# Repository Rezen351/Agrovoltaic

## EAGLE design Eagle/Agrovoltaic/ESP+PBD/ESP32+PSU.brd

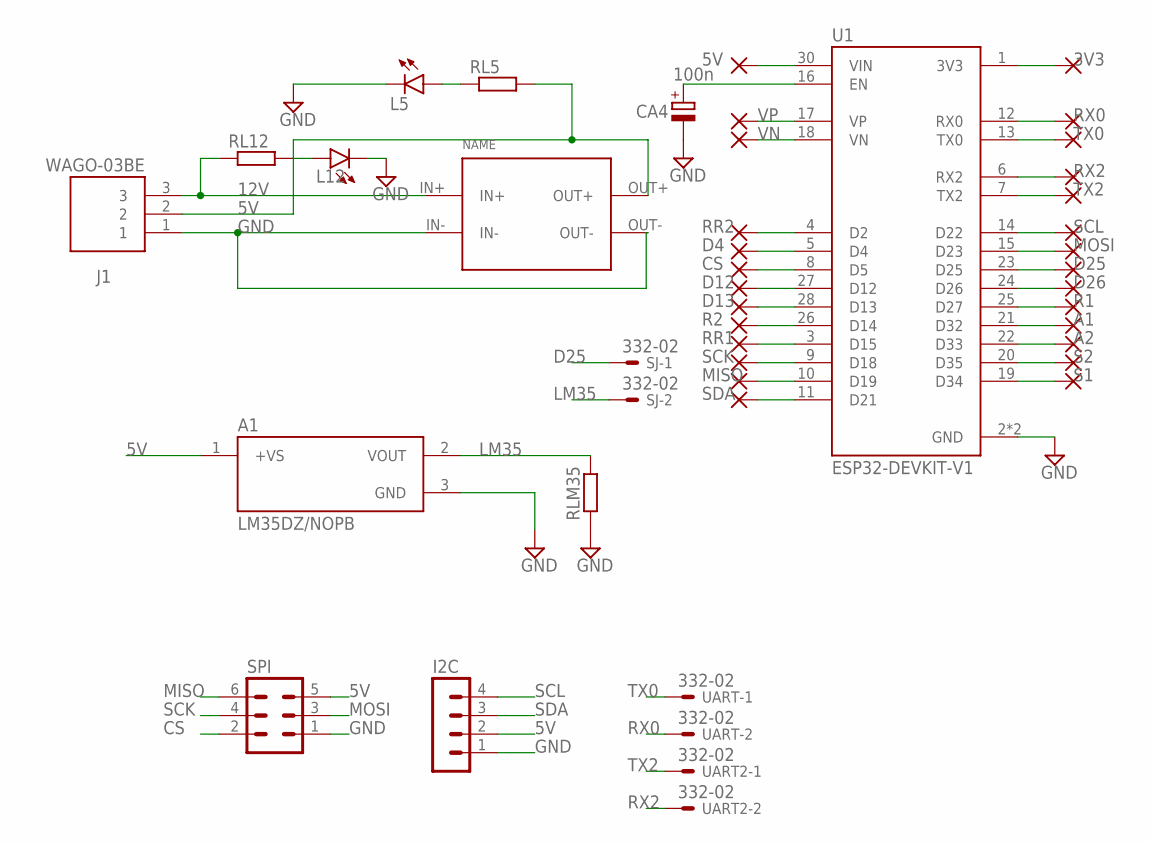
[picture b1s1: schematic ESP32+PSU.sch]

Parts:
A1: LM35DZ/NOPB; TO92127P521H735-3
CA4: 100n; E5-6
I2C: MA04-1
J1: WAGO-03BE; CUI_TB006-508-03BE
L5, L12: LED3MM
PAD1, PAD2, PAD3, PAD4, PAD5, PAD6, PAD7, PAD8, PAD9, PAD10, PAD11, PAD12, PAD13, PAD14, PAD15, PAD16, PAD17, PAD18, PAD19, PAD20, PAD21, PAD22, PAD23, PAD24, PAD25, PAD26, PAD52: WIREPAD1,6/0,9; 1,6/0,9
RL5, RL12: R-EU_0309/12; 0309/12
RLM35: R-EU_0309/12; 0309/12
SJ: 332-02
SPI: MA03-2
U1: ESP32-DEVKIT-V1; MODULE_ESP32_DEVKIT_V1
U$1: CP8-ADJ
UART, UART2: 332-02

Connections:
3V3: PAD11.1, U1.1 (3V3)
5V: A1.1 (+VS), I2C.2, J1.2, PAD25.1, RL5.2, SPI.5, U1.30 (VIN), U$1.OUT+
12V: J1.3, RL12.1, U$1.IN+
A1: PAD21.1, U1.21 (D32)
A2: PAD22.1, U1.22 (D33)
CS: PAD3.1, SPI.2, U1.8 (D5)
D4: PAD2.1, U1.5 (D4)
D12: PAD4.1, U1.27 (D12)
D13: PAD5.1, U1.28 (D13)
D25: PAD18.1, SJ.1, U1.23 (D25)
D26: PAD19.1, U1.24 (D26)
GND: A1.3 (GND), CA4.-, I2C.1, J1.1, L5.K (C), L12.K (C), RLM35.1, SPI.1, U1.2 (GND), U1.29 (GND), U$1.IN-, U$1.OUT-
LM35: A1.2 (VOUT), RLM35.2, SJ.2
MISO: PAD9.1, SPI.6, U1.10 (D19)
MOSI: PAD17.1, SPI.3, U1.15 (D23)
unnamed: L12.A, RL12.2
unnamed: L5.A, RL5.1
unnamed: CA4.+, U1.16 (EN)
R1: PAD20.1, U1.25 (D27)
R2: PAD6.1, U1.26 (D14)
RR1: PAD7.1, U1.3 (D15)
RR2: PAD1.1, U1.4 (D2)
RX0: PAD12.1, U1.12 (RX0), UART.2
RX2: PAD14.1, U1.6 (RX2), UART2.2
S1: PAD24.1, U1.19 (D34)
S2: PAD23.1, U1.20 (D35)
SCK: PAD8.1, SPI.4, U1.9 (D18)
SCL: I2C.4, PAD16.1, U1.14 (D22)
SDA: I2C.3, PAD10.1, U1.11 (D21)
TX0: PAD13.1, U1.13 (TX0), UART.1
TX2: PAD15.1, U1.7 (TX2), UART2.1
VN: PAD52.1, U1.18 (VN)
VP: PAD26.1, U1.17 (VP)

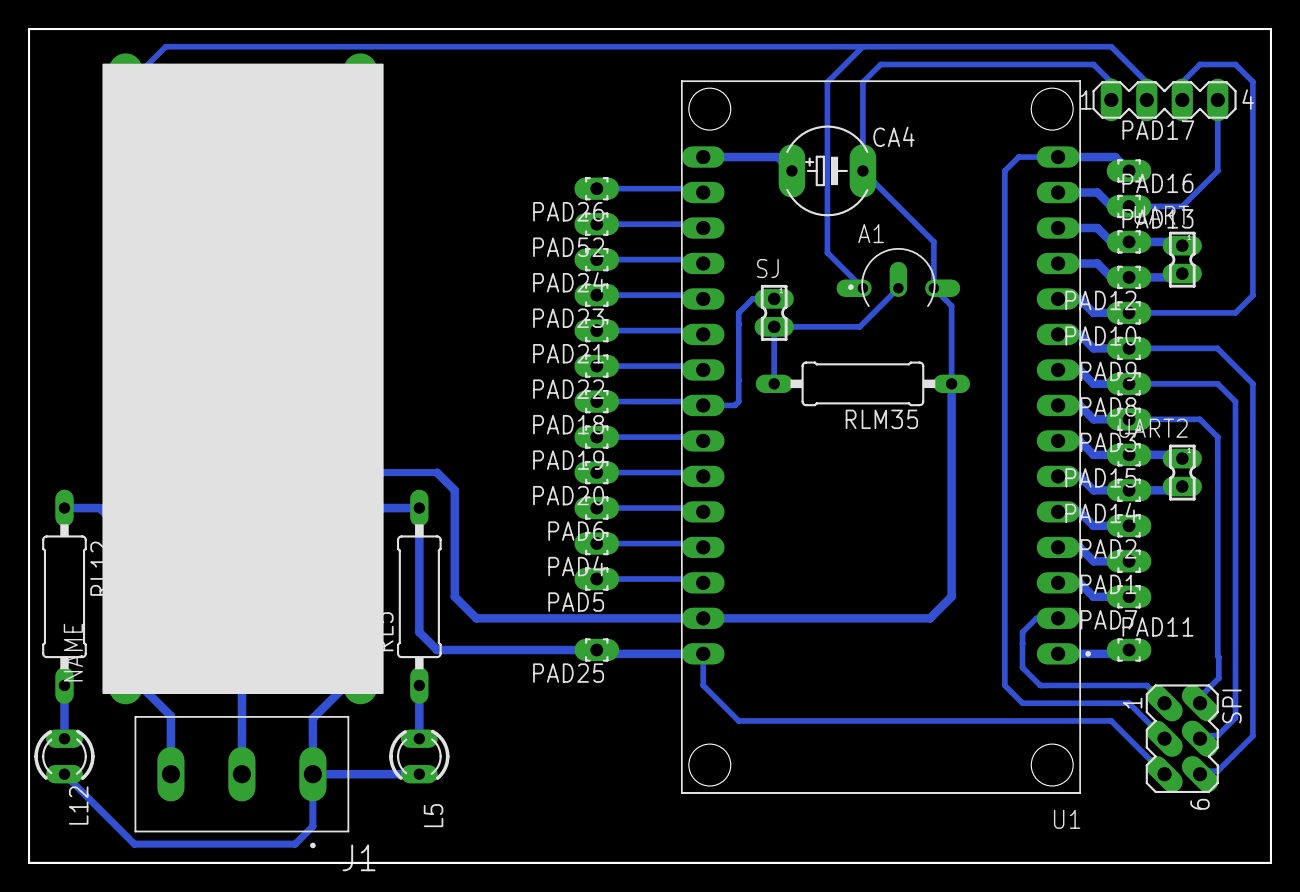
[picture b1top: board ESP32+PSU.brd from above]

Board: 2 copper layers, 88.9 x 59.7 mm, 42 parts (0 on the bottom side), 33 nets.

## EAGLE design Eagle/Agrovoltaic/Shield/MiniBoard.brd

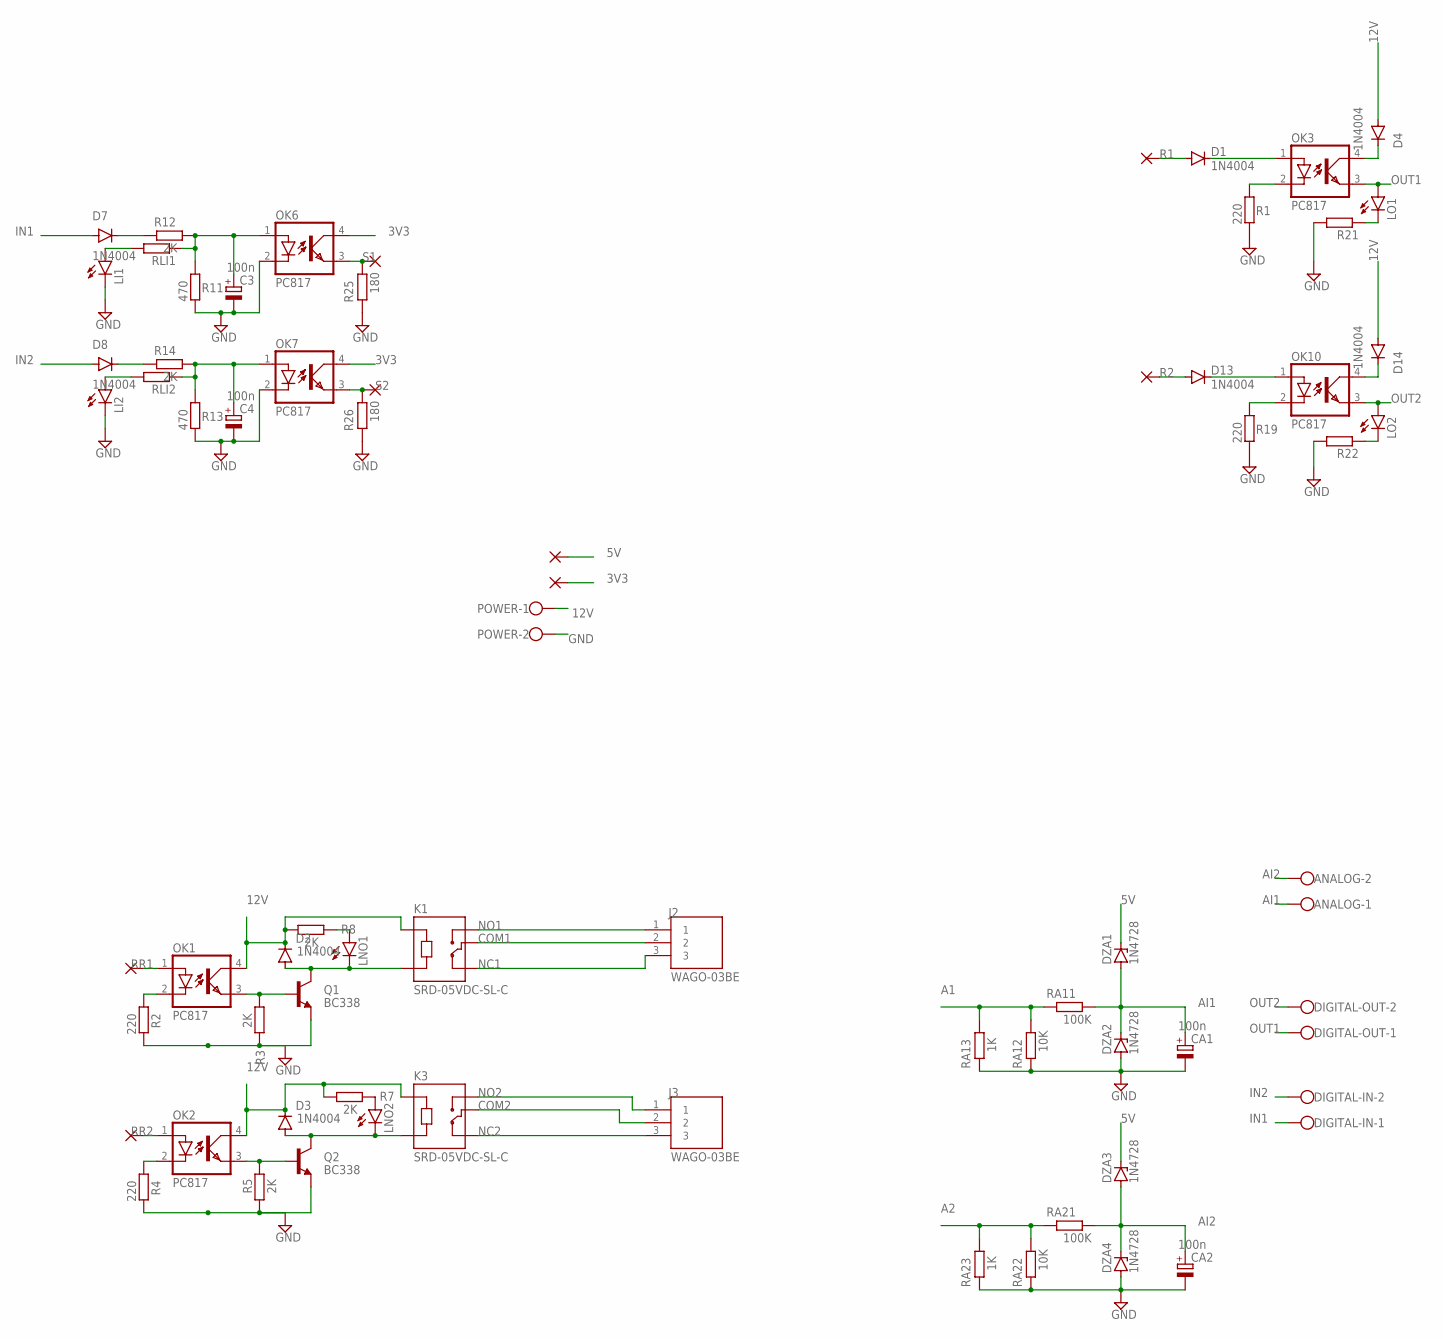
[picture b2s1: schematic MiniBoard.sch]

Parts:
ANALOG: W237-102
C3, C4: 100n; E5-6
CA1, CA2: 100n; E5-6
D1, D2, D3, D4, D7, D8, D13, D14: 1N4004; DO41-10
DIGITAL-IN: W237-102
DIGITAL-OUT: W237-102
DZA1, DZA2, DZA3, DZA4: 1N4728; DO41Z10
J2, J3: WAGO-03BE; CUI_TB006-508-03BE
K1, K3: SRD-05VDC-SL-C; RELAY_SRD-05VDC-SL-C
LI1, LI2: LED3MM
LNO1, LNO2: LED3MM
LO1, LO2: LED3MM
OK1, OK2, OK3, OK6, OK7, OK10: PC817; DIL04
PAD1, PAD2, PAD3, PAD4, PAD5, PAD6, PAD79, PAD80: WIREPAD1,6/0,9; 1,6/0,9
POWER: W237-102
Q1, Q2: BC338; TO92-EBC
R1, R2, R4, R19: 220; 0309/12
R3, R5, R7, R8, R12, R14: 2K; 0309/12
R11, R13: 470; 0309/12
R21, R22: R-EU_0309/12; 0309/12
R25, R26: 180; 0309/12
RA11, RA21: 100K; 0309/12
RA12, RA22: 10K; 0309/12
RA13, RA23: 1K; 0309/12
RLI1, RLI2: R-EU_0309/12; 0309/12

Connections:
3V3: OK6.4 (COL), OK7.4 (COL), PAD5.1
5V: DZA1.C, DZA3.C, PAD6.1
12V: D2.C, D3.C, D4.A, D14.A, K1.A1, K3.A1, OK1.4 (COL), OK2.4 (COL), POWER.1, R7.1, R8.1
A1: RA11.1, RA12.2, RA13.2
A2: RA21.1, RA22.2, RA23.2
AI1: ANALOG.1, CA1.+, DZA1.A, DZA2.C, RA11.2
AI2: ANALOG.2, CA2.+, DZA3.A, DZA4.C, RA21.2
COM1: J2.2, K1.COM
COM2: J3.2, K3.COM
IN1: D7.A, DIGITAL-IN.1
IN2: D8.A, DIGITAL-IN.2
unnamed: OK2.2 (C), R4.1
unnamed: OK1.2 (C), R2.1
unnamed: OK1.3 (EMIT), Q1.B, R3.1
unnamed: D3.A, K3.A2, LNO2.K (C), Q2.C
unnamed: OK2.3 (EMIT), Q2.B, R5.2
unnamed: LNO2.A, R7.2
unnamed: LNO1.A, R8.2
unnamed: D2.A, K1.A2, LNO1.K (C), Q1.C
unnamed: D1.C, OK3.1 (A)
unnamed: OK3.2 (C), R1.1
unnamed: D4.C, OK3.4 (COL)
unnamed: C3.+, OK6.1 (A), R11.1, R12.2, RLI1.1
unnamed: D7.C, R12.1
unnamed: C4.+, OK7.1 (A), R13.1, R14.2, RLI2.1
unnamed: D8.C, R14.1
unnamed: LI2.A, RLI2.2
unnamed: D13.C, OK10.1 (A)
unnamed: OK10.2 (C), R19.1
unnamed: LI1.A, RLI1.2
unnamed: LO1.K (C), R21.1
unnamed: LO2.K (C), R22.1
unnamed: D14.C, OK10.4 (COL)
NC1: J2.3, K1.NC
NC2: J3.3, K3.NC
NO1: J2.1, K1.NO
NO2: J3.1, K3.NO
OUT1: DIGITAL-OUT.1, LO1.A, OK3.3 (EMIT)
OUT2: DIGITAL-OUT.2, LO2.A, OK10.3 (EMIT)
R1: D1.A, PAD79.1
R2: D13.A, PAD80.1
RR1: OK1.1 (A), PAD4.1
RR2: OK2.1 (A), PAD3.1
S1: OK6.3 (EMIT), PAD1.1, R25.2
S2: OK7.3 (EMIT), PAD2.1, R26.2

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
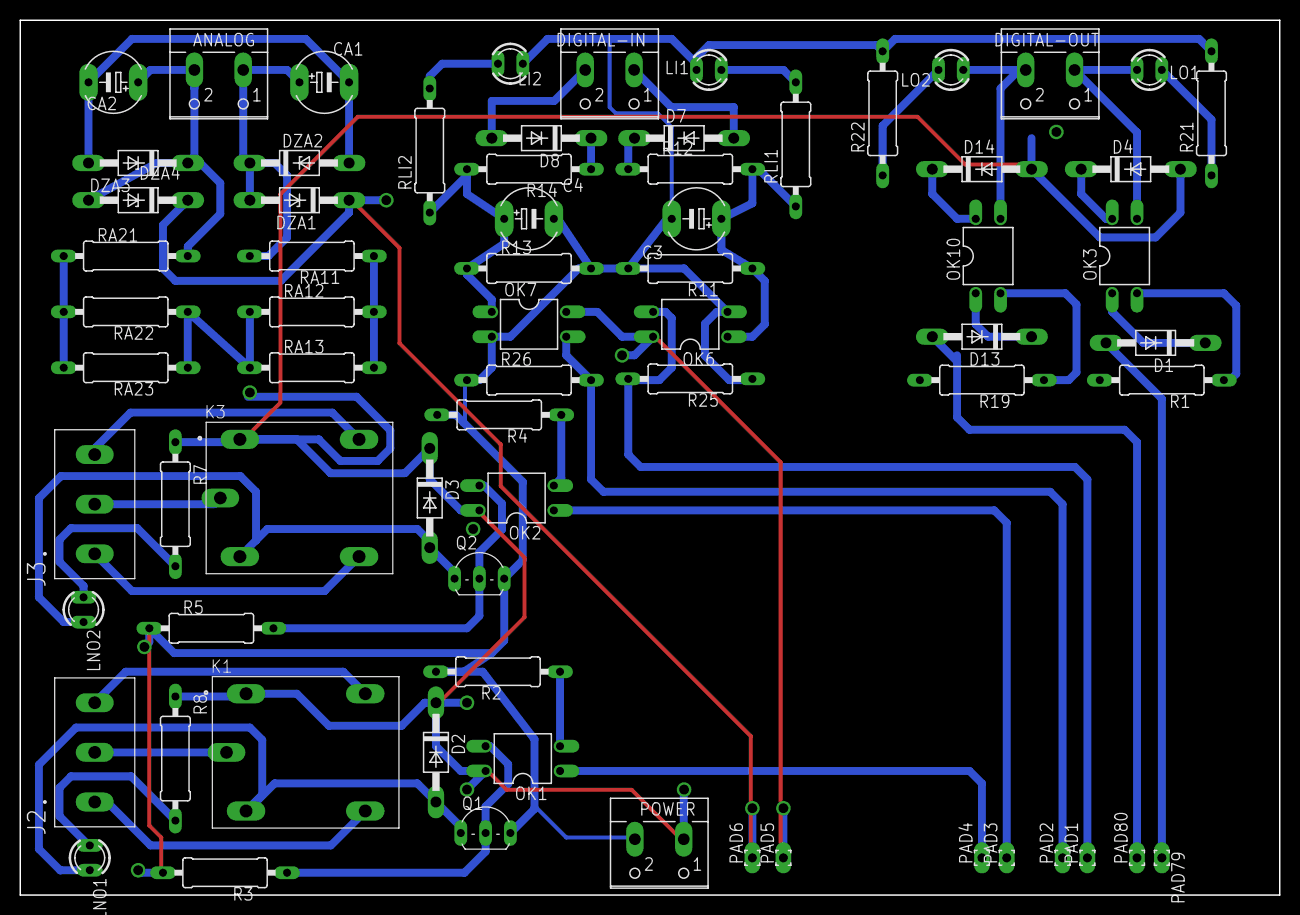
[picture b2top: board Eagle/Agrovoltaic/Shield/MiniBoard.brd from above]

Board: 2 copper layers, 128.9 x 89.5 mm, 70 parts (0 on the bottom side), 48 nets.

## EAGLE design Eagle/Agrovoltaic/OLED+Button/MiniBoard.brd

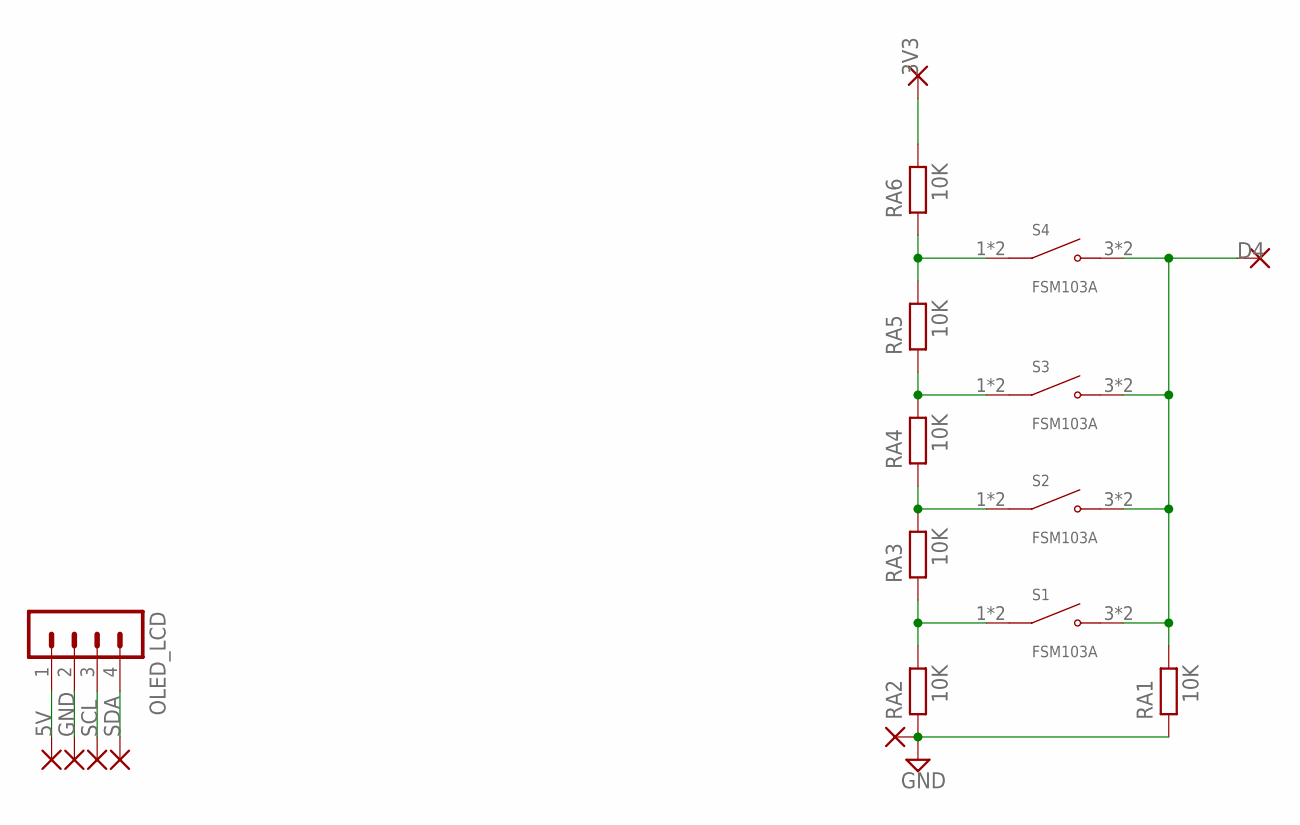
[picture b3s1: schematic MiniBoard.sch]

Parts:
OLED_LCD: MA04-1
PAD1, PAD25, PAD26, PAD52, PAD78, PAD103, PAD104: WIREPAD1,6/0,9; 1,6/0,9
RA1, RA2, RA3, RA4, RA5, RA6: 10K; 0309/12
S1, S2, S3, S4: FSM103A; SW_1571627-1

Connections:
3V3: PAD104.1, RA6.2
5V: OLED_LCD.1, PAD25.1
D4: PAD103.1, RA1.2, S1.3 (NO), S1.4 (NO), S2.3 (NO), S2.4 (NO), S3.3 (NO), S3.4 (NO), S4.3 (NO), S4.4 (NO)
GND: OLED_LCD.2, PAD1.1, PAD26.1, RA1.1, RA2.1
unnamed: RA4.2, RA5.1, S3.1 (COM), S3.2 (COM)
unnamed: RA3.2, RA4.1, S2.1 (COM), S2.2 (COM)
unnamed: RA2.2, RA3.1, S1.1 (COM), S1.2 (COM)
unnamed: RA5.2, RA6.1, S4.1 (COM), S4.2 (COM)
SCL: OLED_LCD.3, PAD52.1
SDA: OLED_LCD.4, PAD78.1

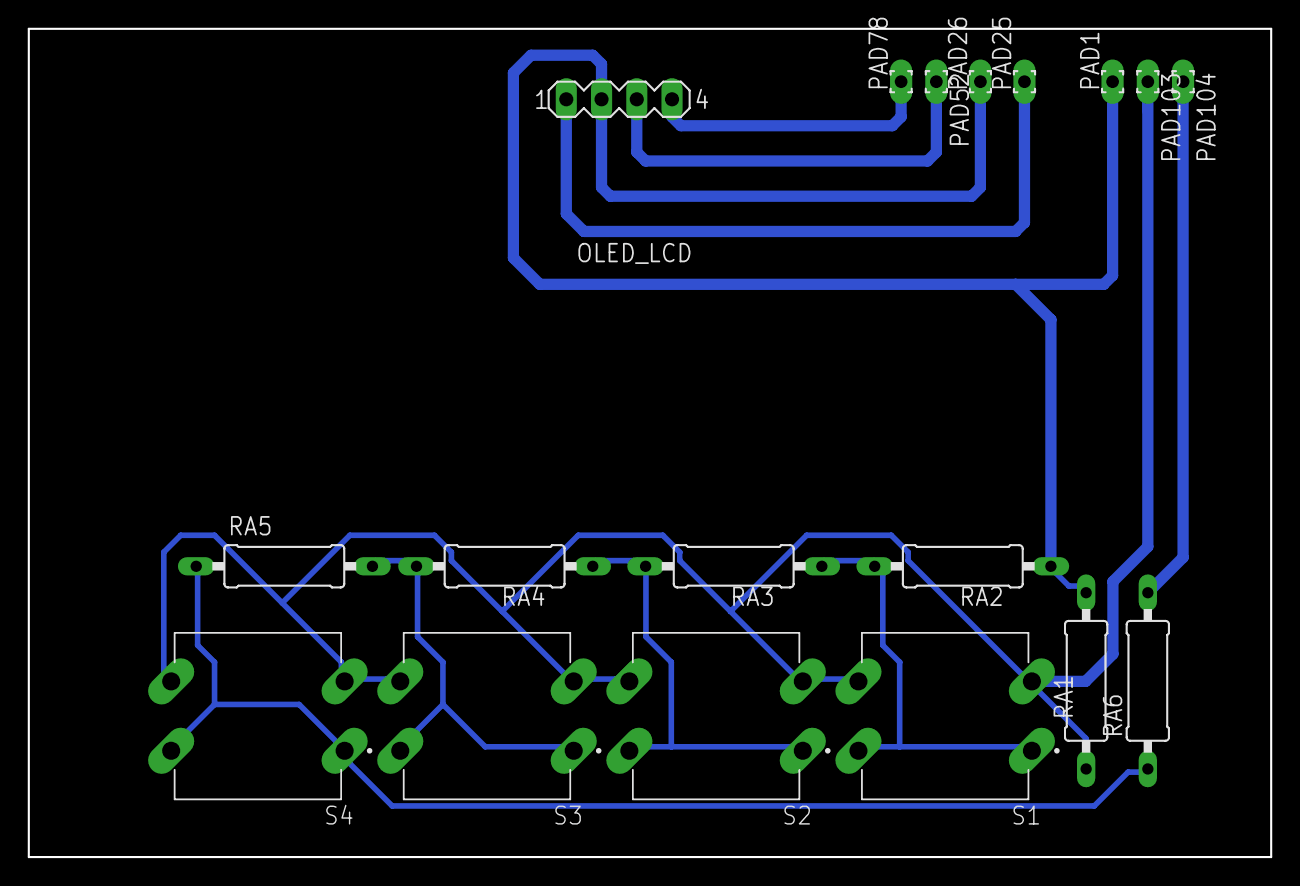
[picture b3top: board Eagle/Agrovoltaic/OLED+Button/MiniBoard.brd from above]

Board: 2 copper layers, 89.5 x 59.7 mm, 18 parts (0 on the bottom side), 10 nets.

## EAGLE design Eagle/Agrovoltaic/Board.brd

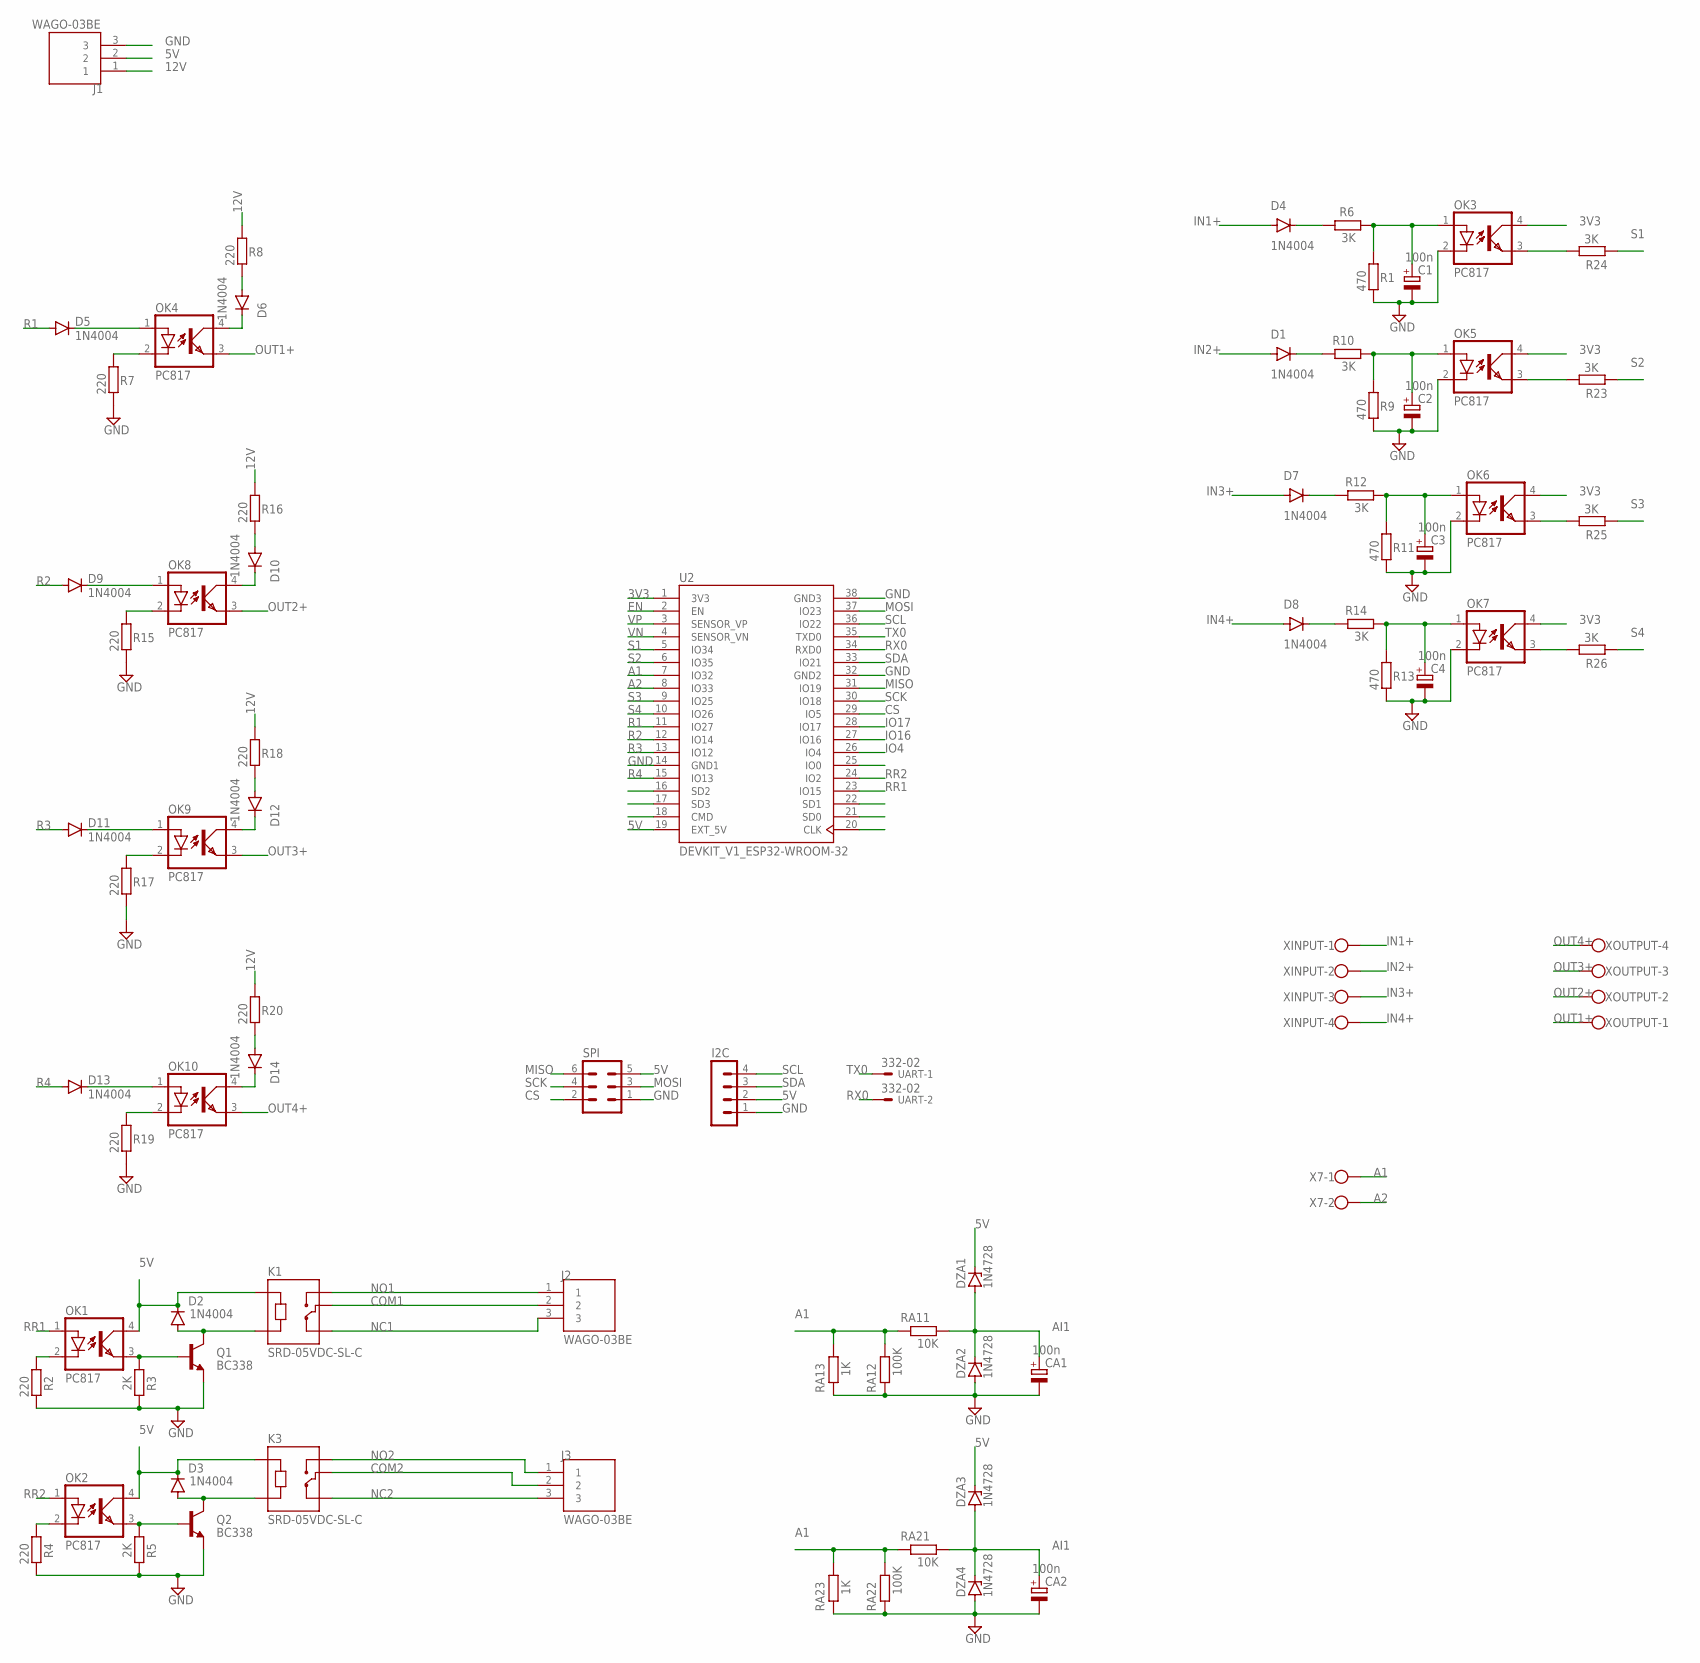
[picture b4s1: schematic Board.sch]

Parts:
C1, C2, C3, C4: 100n; E3,5-8
CA1, CA2: 100n; E3,5-8
D1, D2, D3, D4, D5, D6, D7, D8, D9, D10, D11, D12, D13, D14: 1N4004; DO41-10
DZA1, DZA2, DZA3, DZA4: 1N4728; DO41Z10
I2C: MA04-1
J1, J2, J3: WAGO-03BE; CUI_TB006-508-03BE
K1, K3: SRD-05VDC-SL-C; RELAY_SRD-05VDC-SL-C
OK1, OK2, OK3, OK4, OK5, OK6, OK7, OK8, OK9, OK10: PC817; DIL04
Q1, Q2: BC338; TO92-EBC
R1, R9, R11, R13: 470; 0207/10
R2, R4, R7, R8, R15, R16, R17, R18, R19, R20: 220; 0207/10
R3, R5: 2K; 0207/10
R6, R10, R12, R14, R23, R24, R25, R26: 3K; 0207/10
RA11, RA21: 10K; 0207/10
RA12, RA22: 100K; 0207/10
RA13, RA23: 1K; 0207/10
SPI: MA03-2
U2: DEVKIT_V1_ESP32-WROOM-32; MODULE_DEVKIT_V1_ESP32-WROOM-32
UART: 332-02
X7: W237-102
XINPUT: W237-4
XOUTPUT: W237-4

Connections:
3V3: OK3.4 (COL), OK5.4 (COL), OK6.4 (COL), OK7.4 (COL), U2.1 (3V3)
5V: D2.C, D3.C, DZA1.C, DZA3.C, I2C.2, J1.2, K1.A1, K3.A1, OK1.4 (COL), OK2.4 (COL), SPI.5, U2.19 (EXT_5V)
12V: J1.1, R8.1, R16.1, R18.1, R20.1
A1: RA11.1, RA12.2, RA13.2, RA21.1, RA22.2, RA23.2, U2.7 (IO32), X7.1
A2: U2.8 (IO33), X7.2
AI1: CA1.+, CA2.+, DZA1.A, DZA2.C, DZA3.A, DZA4.C, RA11.2, RA21.2
COM1: J2.2, K1.COM
COM2: J3.2, K3.COM
CS: SPI.2, U2.29 (IO5)
EN: U2.2 (EN)
GND: C1.-, C2.-, C3.-, C4.-, CA1.-, CA2.-, DZA2.A, DZA4.A, I2C.1, J1.3, OK3.2 (C), OK5.2 (C), OK6.2 (C), OK7.2 (C), Q1.E, Q2.E, R1.2, R2.2, R3.2, R4.2, R5.2, R7.2, R9.2, R11.2, R13.2, R15.2, R17.2, R19.2, RA12.1, RA13.1, RA22.1, RA23.1, SPI.1, U2.14 (GND1), U2.32 (GND2), U2.38 (GND3)
IN1+: D4.A, XINPUT.1
IN2+: D1.A, XINPUT.2
IN3+: D7.A, XINPUT.3
IN4+: D8.A, XINPUT.4
IO4: U2.26 (IO4)
IO16: U2.27 (IO16)
IO17: U2.28 (IO17)
MISO: SPI.6, U2.31 (IO19)
MOSI: SPI.3, U2.37 (IO23)
unnamed: OK2.2 (C), R4.1
unnamed: OK1.2 (C), R2.1
unnamed: OK1.3 (EMIT), Q1.B, R3.1
unnamed: D2.A, K1.A2, Q1.C
unnamed: OK5.3 (EMIT), R23.2
unnamed: OK2.3 (EMIT), Q2.B, R5.1
unnamed: D3.A, K3.A2, Q2.C
unnamed: OK3.3 (EMIT), R24.2
unnamed: C1.+, OK3.1 (A), R1.1, R6.2
unnamed: D5.C, OK4.1 (A)
unnamed: D4.C, R6.1
unnamed: OK4.2 (C), R7.1
unnamed: D6.A, R8.2
unnamed: C2.+, OK5.1 (A), R9.1, R10.2
unnamed: D1.C, R10.1
unnamed: C3.+, OK6.1 (A), R11.1, R12.2
unnamed: D7.C, R12.1
unnamed: C4.+, OK7.1 (A), R13.1, R14.2
unnamed: D8.C, R14.1
unnamed: D9.C, OK8.1 (A)
unnamed: OK8.2 (C), R15.1
unnamed: D10.A, R16.2
unnamed: D11.C, OK9.1 (A)
unnamed: OK9.2 (C), R17.1
unnamed: D12.A, R18.2
unnamed: D13.C, OK10.1 (A)
unnamed: OK10.2 (C), R19.1
unnamed: D14.A, R20.2
unnamed: D12.C, OK9.4 (COL)
unnamed: OK6.3 (EMIT), R25.2
unnamed: OK7.3 (EMIT), R26.2
unnamed: D14.C, OK10.4 (COL)
unnamed: D10.C, OK8.4 (COL)
unnamed: D6.C, OK4.4 (COL)
NC1: J2.3, K1.NC
NC2: J3.3, K3.NC
NO1: J2.1, K1.NO
NO2: J3.1, K3.NO
OUT1+: OK4.3 (EMIT), XOUTPUT.1
OUT2+: OK8.3 (EMIT), XOUTPUT.2
OUT3+: OK9.3 (EMIT), XOUTPUT.3
OUT4+: OK10.3 (EMIT), XOUTPUT.4
R1: D5.A, U2.11 (IO27)
R2: D9.A, U2.12 (IO14)
R3: D11.A, U2.13 (IO12)
R4: D13.A, U2.15 (IO13)
RR1: OK1.1 (A), U2.23 (IO15)
RR2: OK2.1 (A), U2.24 (IO2)
RX0: U2.34 (RXD0), UART.2
S1: R24.1, U2.5 (IO34)
S2: R23.1, U2.6 (IO35)
S3: R25.1, U2.9 (IO25)
S4: R26.1, U2.10 (IO26)
SCK: SPI.4, U2.30 (IO18)
SCL: I2C.4, U2.36 (IO22)
SDA: I2C.3, U2.33 (IO21)
TX0: U2.35 (TXD0), UART.1
VN: U2.4 (SENSOR_VN)
VP: U2.3 (SENSOR_VP)

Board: 2 copper layers, 78 parts (0 on the bottom side), 73 nets, no tracks yet.

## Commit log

2024-12-06 edit
2024-12-07 ADD:Menambahkan Desain
2024-12-08 EDIT:Mengedit Board
2024-12-08 ADD:Edit Mini Board
2024-12-09 EDIT:Melanjutkan
2024-12-09 Still Edit
2024-12-10 ADD:Library
2024-12-10 rapihin beberapa bagian, agar mudah diwire
2024-12-10 MODIFY:Memisahkan Space Board
2024-12-11 FINISHING
2024-12-12 ADD: Logo
2024-12-13 REV:Revisi rangkaian 1
2024-12-13 Revisi lagiii
2024-12-14 Revisi lagi lamp ke colector relay
2024-12-15 Revisi board dan revisi wiring diagram
2025-01-21 Revisi
2025-01-24 Alur Program.drawio
2025-01-24 Added Flow Program.drawio
2025-01-25 ADD:Menambahkan pembacaan data
2025-01-25 ADD: Menambahkan json wraping content
2025-02-18 ADD : Menambahkan fitur menu OLED
2025-03-13 Modifikasi main
2025-03-13 menambahkan mqtt wifi
